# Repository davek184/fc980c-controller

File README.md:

# FC980C Controller
Design modifications are based on parent [project](https://github.com/wlhlm/fc980c-controller).  

Similar concept to Hasu 980c controller but it is a nice upgrade in processing limitations vs the Atmega32u4.

Related project [USB-C Daughterboard](https://github.com/davek184/980_Usb_C_Daughterboard)

## Warning!!!
There was something wrong with the last 2 batches of these.  2 out of 5 would not properly register the keyboard after flashing.  It was unclear if this a manufacturing mistake from JLCPCB or an issue with the compontents.  Did NOT have time to look into it further, use at your own risk!

## Changes
* Added USB SH Connector
* Added USB Molex EZ-Mate connector
* Added RGB Underglow support (Norbauer Heavy-9 is the only case I know of that could take advantage of this)
* Added MegaMan logo
* Altered Boot0 so it can be shorted with tweezers for those who don't want to solder a switch
* Altered ISP header

## Firmware
* [Precompiled Firmware](/firmware)
* Can also be compiled into QMK or VIAL firmware yourself using files in the [firmware](/firmware/fc980c) directory

Firmware can be flashed with QMK Toolbox.  To get into bootloader mode short the BootO pins (or press and hold the reset switch) **WHILE connecting the USB cable**

## Manufacturing
* Files are set up for JLCPCB.  
* Select Specify a location for Remove Order Number (that will put it in a set location)
* Choose PCB Assembly
  * Assemble top Side
  * Tooling holes Added by customer
  * Confirm parts placement Yes
* Optional Parts
  * J1 The USB Molex EZ-mate connector, is optional and can be deselected to save some money
  * J4 The USB SH connector, is optional and can be deselected to save some money
  * J5 The RGB underglow connector, is optional and can be deselected to save some money

**Note the keyboard connector is not available at this time to be assembled.  It must be soldered by yourself!**

Hirose part number DF14-20P-1.25H(52).  Mouser: https://www.mouser.com/ProductDetail/798-DF1420P125H52

_(This is the same keyboard connector the FC660c uses)_

## Thank you
Thank you to [wlhlm](https://github.com/wlhlm) for all the work that went into this.

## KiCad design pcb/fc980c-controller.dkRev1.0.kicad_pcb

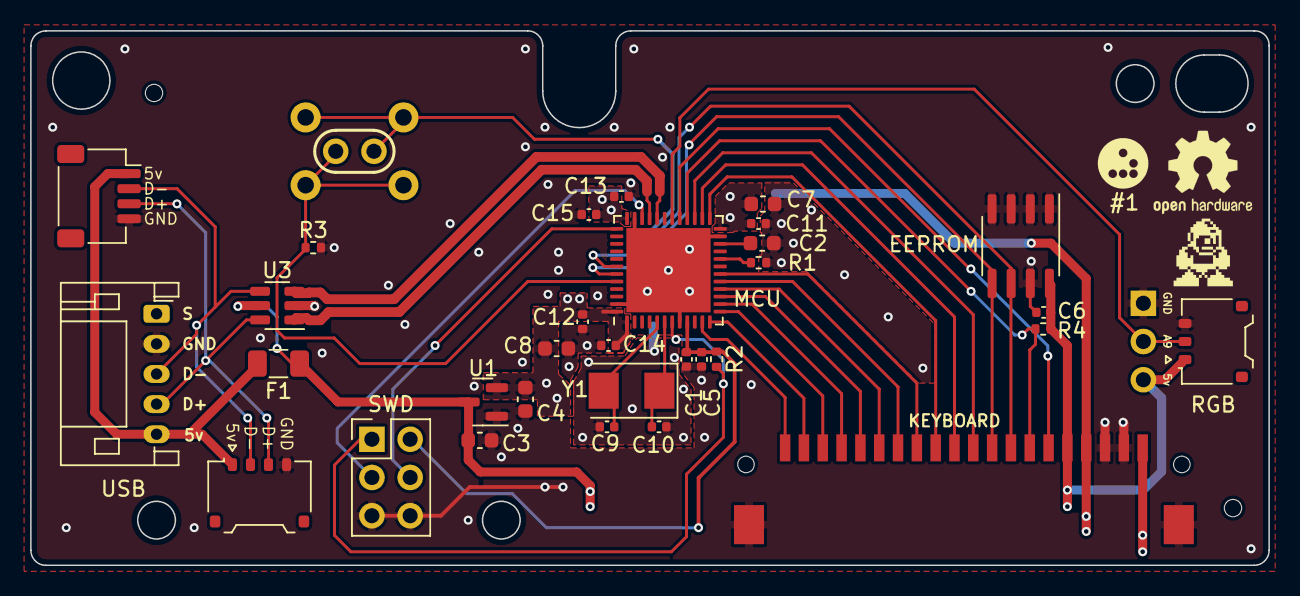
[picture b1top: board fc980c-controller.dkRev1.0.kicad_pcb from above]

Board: 2 copper layers, 82.2 x 35.5 mm, 37 parts (1 on the bottom side), 32 nets.

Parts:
C1: 1uF; C_0402_1005Metric
C2: 4.7uF; C_0603_1608Metric
C3, C4, C8: 1uF; C_0603_1608Metric
C5, C6, C11, C12, C13, C14, C15: 100nF; C_0402_1005Metric
C7: 10uF; C_0603_1608Metric
C9, C10: 20pF; C_0402_1005Metric
F1: 500mA; Fuse_1206_3216Metric
H1, H2: JLC tooling hole; JLC_tooling_hole
J1: Molex_Pico-EZmate_78171-0004_1x04-1MP_P1.20mm_Ver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; Molex_Pico-EZmate_78171-0004_1x04-1MP_P1.20mm_Vertical
J2: USB; JST_PH_S5B-PH-K_1x05_P2.00mm_Horizontal
J3: KEYBOARD; HRS_DF14_20P
J4: JST_SH_SM04B-SRSS-TB_1x04-1MP_P1.00mm_Horizontal
J5: Molex_Pico-EZmate_78171-0003_1x03-1MP_P1.20mm_Ver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; Molex_Pico-EZmate_78171-0003_1x03-1MP_P1.20mm_Vertical
J6: PinHeader_1x03_P2.54mm_Vertical
LOGO1: Logo_Open_Hardware_Small; OSHW-Logo2_7.3x6mm_SilkScreen
R1, R2, R3, R4: 10k; R_0402_1005Metric
SW1: PinHeader_1x02_P2.54mm_Vertical
SW1#2: BOOT0; SW_PUSH_6mm
SWD: PinHeader_2x03_P2.54mm_Vertical
U1: XC6206P332MR; SOT-23
U2: STM32F401CBUx; QFN-48-1EP_7x7mm_P0.5mm_EP5.6x5.6mm
U3: USBLC6-2SC6; SOT-23-6
U4: M24C64-RMN6TP; SOIC-8_3.9x4.9mm_P1.27mm
Y1: 8MHz Cl 20pF; Crystal_SMD_5032-2Pin_5.0x3.2mm

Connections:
+5V: C3.1, C6.1, F1.1, J3.16, J5.1, J6.3, R4.1, U1.3 (VI), U3.5 (VBUS), U4.8 (VCC)
/BOOT1: R1.1, U2.20 (PB2)
/VCAP1: C2.1, U2.22 (VCAP1)
BOOT0: R3.1, SW1.1, SW1#2.2, U2.44 (BOOT0)
COL_BIT0: J3.8, U2.18 (PB0)
COL_BIT1: J3.9, U2.25 (PB12)
COL_BIT2: J3.10, U2.26 (PB13)
COL_BIT3: J3.11, U2.27 (PB14)
D_N: U2.32 (PA11), U3.3 (I/O2)
D_P: U2.33 (PA12), U3.1 (I/O1)
D_USB_N: J1.2, J2.3, J4.2, U3.4 (I/O2)
D_USB_P: J1.3, J2.4, J4.3, U3.6 (I/O1)
FG: J2.1, J3.20
GND: C1.2, C2.2, C3.2, C4.2, C5.2, C6.2, C7.2, C8.2, C9.2, C10.2, C11.2, C12.2, C13.2, C14.2, C15.2, J1.4, J2.2, J3.18, J3.19, J3.21, J3.22, J4.4, J5.3, J6.1, R1.2, R3.2, SWD.5, SWD.6, U1.1 (GND), U2.8 (VSSA), U2.23 (VSS), U2.35 (VSS), U2.47 (VSS), U2.49 (VSS), U3.2 (GND), U4.1 (E0), U4.2 (E1), U4.3 (E2), U4.4 (VSS), U4.7 (~WC)
I2C_SCL: J3.13, U2.42 (PB6), U4.6 (SCL)
I2C_SDA: J3.12, U2.43 (PB7), U4.5 (SDA)
KEY_ENABLE: J3.4, U2.14 (PA4)
KEY_HYS: J3.15, U2.29 (PA8)
KEY_STATE: J3.14, R4.2, U2.28 (PB15)
LED_CAPS: J3.2, U2.12 (PA2)
LED_NUM: J3.3, U2.13 (PA3)
LED_SCRL: J3.1, U2.11 (PA1)
ROW_BIT0: J3.5, U2.15 (PA5)
ROW_BIT1: J3.6, U2.16 (PA6)
ROW_BIT2: J3.7, U2.17 (PA7)
SWCLK: SWD.4, U2.37 (PA14)
SWDIO: SWD.3, U2.34 (PA13)
VBUS: F1.2, J1.1, J2.5, J4.1
VDDA: C1.1, C4.1, C5.1, C7.1, C8.1, C11.1, C12.1, C13.1, C14.1, C15.1, J3.17, R2.1, SW1.2, SW1#2.1, SWD.2, U1.2 (VO), U2.1 (VBAT), U2.9 (VREF+), U2.24 (VDD), U2.36 (VDD), U2.48 (VDD)
XTAL_IN: C9.1, U2.5 (PH0), Y1.2
XTAL_OUT: C10.1, U2.6 (PH1), Y1.1
~RESET: R2.2, SWD.1, U2.7 (NRST)

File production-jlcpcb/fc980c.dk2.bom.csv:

Designator,Footprint,Quantity,Value,LCSC Part #
"C1",0402,1,1uF,C52923
"C9, C10",0402,1,20pF,C1554
"C5,C6,C11,C12,C13,C14,C15"0402,1,100nF,C1525
"C2",0603,1,4.7uF,C19666
"C3,C4,C8", 0603,1,1uF,C15849
"C7",0603,1,10uF,C19702
"F1",1206,1,500mA,C70076
"J1",Molex_Pico-EZmate_78171-0004_1x04-1MP_P1.20mm_Vertical,1,Molex_Pico-EZmate_78171-0004_1x04-1MP_P1.20mm_Vertical,C528030
"J2",JST_PH_S5B-PH-K_1x05_P2.00mm_Horizontal,1,USB,
"J4",JST_SH_SM04B-SRSS-TB_1x04-1MP_P1.00mm_Horizontal,1,JST_SH_SM04B-SRSS-TB_1x04-1MP_P1.00mm_Horizontal,C160404
"J5",Molex_Pico-EZmate_78171-0003_1x03-1MP_P1.20mm_Vertical,1,Molex_Pico-EZmate_78171-0003_1x03-1MP_P1.20mm_Vertical,C528029
"R1,R2,R3,R4", 0402,1,10k,C25744
"U1",SOT-23,1,XC6206P332MR,C5446
"U2",QFN-48-1EP_7x7mm_P0.5mm_EP5.6x5.6mm,1,STM32F401CBUx,C118825
"U3",SOT-23-6,1,USBLC6-2SC6,C2827654
"U4",SOIC-8_3.9x4.9mm_P1.27mm,1,M24C64-RMN6TP,C79988
"Y1",Crystal_SMD_5032-2Pin_5.0x3.2mm,1,8MHz Cl 20pF,C115962

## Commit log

2023-03-30 DK Revision
    * Rounded PCB corners,
    * Added USB connectors JST SH
    * Added USB connectors Molex EZ-mate
    * Added RGB underglow
2023-03-31 Added JST PH Connector to BOM & Position file
2023-03-31 Spelling
2024-01-18 Vial Firmware Update
    Firmware compatible with the latest VIAL repo
2024-01-18 Update README.md
    Added warning

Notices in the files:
pcb/fc980c-controller.dkRev1.0.kicad_pcb:
Licensed under CERN-OHL-S V2
© 2023 W. Schuster
